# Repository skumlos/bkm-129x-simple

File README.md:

A simplified version of the BKM-129X compatible board.

Revision B

Should be able to be created at $25-30, with the ADG1611 being the most expensive component.

This requires an Arduino Nano v3 loaded with the latest BKM-129X-MCU code from https://github.com/skumlos/bkm-129x-mcu

For more information go to https://immerhax.com/?p=422

You are welcome to clone, produce and sell hardware based on this. Please keep changes and so on open source.

Cool kids give credit where due.

Thanks goes out to Nick Carney and Bob from RetroRGB for rigorious testing!

--------

Compatibility list and tested consoles (including issues):

PVM-9L2
- SNES (US region, CSYNC)
- Mega Drive 2 (EU region, 60 Hz modded with DFO for "true" 60 Hz, CSYNC)
- Master System 1 (EU region, 60 Hz modded with DFO for "true" 60 Hz, CSYNC)
- PC-Engine (White, with THS7374 external RGB amp, CSYNC)

BVM-D14
- Genesis 1 (60 Hz, CSYNC)

BVM-D9
- Nomad (60 Hz, Triple bypass modded, CSYNC)
- SNES (US region, CSYNC)
- Master System (60 Hz, sync issues like original 129X)
- TurboGrafx/PC-Engine (60 Hz, sync issues like original 129X)

---------

Board revision history:

C: Rearranged some components for nicer layout

B: Added R29, R30, R31 to compensate for overbrightness

A: Changed R9 to 0 Ohm / jumper

---------

Copyright © 2020 Martin Hejnfelt <martin@hejnfelt.com>
This work is free. You can redistribute it and/or modify it under the
terms of the Do What The Fuck You Want To Public License, Version 2,
as published by Sam Hocevar. See the LICENSE file for more details.

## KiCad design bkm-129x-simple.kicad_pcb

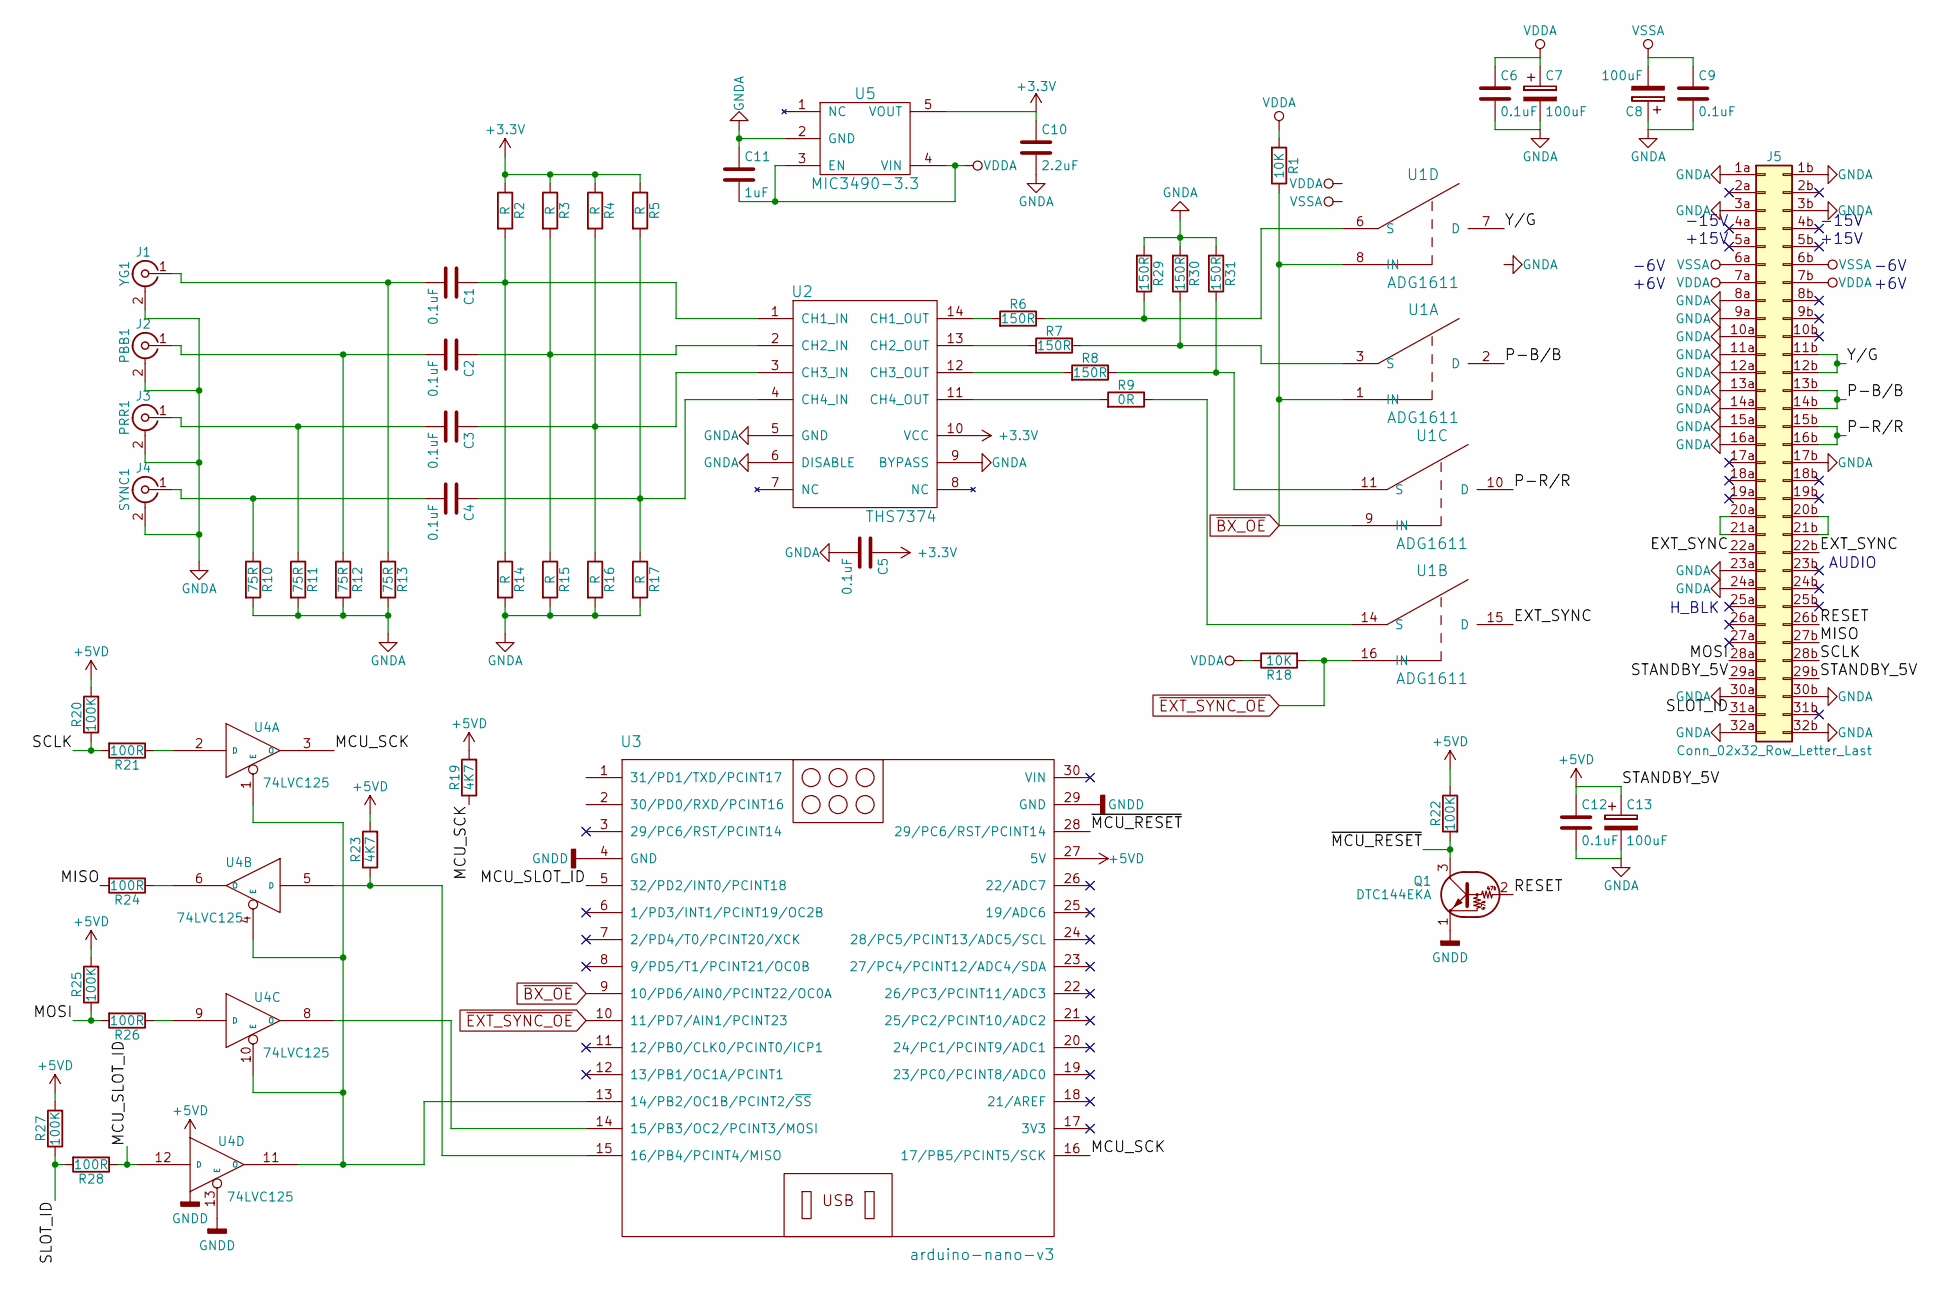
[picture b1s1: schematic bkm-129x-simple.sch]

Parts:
C1, C2, C3, C4, C5, C6, C9, C12: 0.1uF; C_0805_HandSoldering
C7, C8, C13: 100uF; CP_Elec_6.3x5.3
C10: 2.2uF; C_0805_HandSoldering
C11: 1uF; C_0805_HandSoldering
J1: YG1; BNC-THT
J2: PBB1; BNC-THT
J3: PRR1; BNC-THT
J4: SYNC1; BNC-THT
J5: Conn_02x32_Row_Letter_Last; DIN-41612-64P
Q1: DTC144EKA; SC-59_Handsoldering
R1, R18: 10K; R_0805_HandSoldering
R2, R3, R4, R5, R14, R15, R16, R17: R; R_0805_HandSoldering
R6, R7, R8, R29, R30, R31: 150R; R_0805_HandSoldering
R9: 0R; R_0805_HandSoldering
R10, R11, R12, R13: 75R; R_0805_HandSoldering
R19, R23: 4K7; R_0805_HandSoldering
R20, R22, R25, R27: 100K; R_0805_HandSoldering
R21, R24, R26, R28: 100R; R_0805_HandSoldering
U1: ADG1611; TSSOP-16_4.4x5mm_Pitch0.65mm
U2: THS7374; TSSOP-14_4.4x5mm_Pitch0.65mm
U3: arduino-nano-v3
U4: 74LVC125; TSSOP-14_4.4x5mm_Pitch0.65mm
U5: MIC3490-3.3; SOT-23-5_HandSoldering

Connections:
+5VD: C12.1, C13.1, J5.29a, J5.29b, R19.2, R20.2, R22.1, R23.2, R25.2, R27.2, U3.27 (5V), U4.14 (VCC)
/EXT_SYNC: J5.22a, J5.22b, U1.15 (D)
/MCU_SCK: R19.1, U3.16 (17/PB5/PCINT5/SCK), U4.3 (O)
/MCU_SLOT_ID: R28.1, U3.5 (32/PD2/INT0/PCINT18), U4.12 (D)
/MISO: J5.27b, R24.2
/MOSI: J5.28a, R25.1, R26.2
/P-B/B: J5.13b, J5.14b, U1.2 (D)
/P-R/R: J5.15b, J5.16b, U1.10 (D)
/RESET: J5.26b, Q1.2 (B)
/SCLK: J5.28b, R20.1, R21.2
/SLOT_ID: J5.31a, R27.1, R28.2
/Y/G: J5.11b, J5.12b, U1.7 (D)
/~MCU_RESET: Q1.3 (C), R22.2, U3.28 (29/PC6/RST/PCINT14)
unnamed: C1.1, R2.2, R14.1, U2.1 (CH1_IN)
unnamed: C1.2, J1.1 (In), R13.1
unnamed: C2.1, R3.2, R15.1, U2.2 (CH2_IN)
unnamed: C2.2, J2.1 (In), R12.1
unnamed: C3.1, R4.2, R16.1, U2.3 (CH3_IN)
unnamed: C3.2, J3.1 (In), R11.1
unnamed: C4.1, R5.2, R17.1, U2.4 (CH4_IN)
unnamed: C4.2, J4.1 (In), R10.1
unnamed: J5.20a, J5.21a
unnamed: J5.20b, J5.21b
unnamed: R6.2, U2.14 (CH1_OUT)
unnamed: R7.2, U2.13 (CH2_OUT)
unnamed: R8.2, U2.12 (CH3_OUT)
unnamed: R9.1, U1.14 (S)
unnamed: R9.2, U2.11 (CH4_OUT)
unnamed: R21.1, U4.2 (D)
unnamed: R23.1, U3.15 (16/PB4/PCINT4/MISO), U4.5 (D)
unnamed: R24.1, U4.6 (O)
unnamed: R26.1, U4.9 (D)
unnamed: R6.1, R29.1, U1.6 (S)
unnamed: R7.1, R30.1, U1.3 (S)
unnamed: R8.1, R31.1, U1.11 (S)
unnamed: U3.13 (14/PB2/OC1B/PCINT2/~SS), U4.1 (E), U4.4 (E), U4.10 (E), U4.11 (O)
unnamed: U3.14 (15/PB3/OC2/PCINT3/MOSI), U4.8 (O)
VDD: C6.1, C7.1, C11.2, J5.7a, J5.7b, R1.2, R18.1, U1.13 (VDD), U5.3 (EN), U5.4 (VIN)
VSS: C8.2, C9.1, J5.6a, J5.6b, U1.4 (VSS)
~BX_OE: R1.1, U1.1 (IN), U1.8 (IN), U1.9 (IN), U3.9 (10/PD6/AIN0/PCINT22/OC0A)
~EXT_SYNC_OE: R18.2, U1.16 (IN), U3.10 (11/PD7/AIN1/PCINT23)

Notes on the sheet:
-15V
+15V
-6V
+6V
AUDIO
H_BLK

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
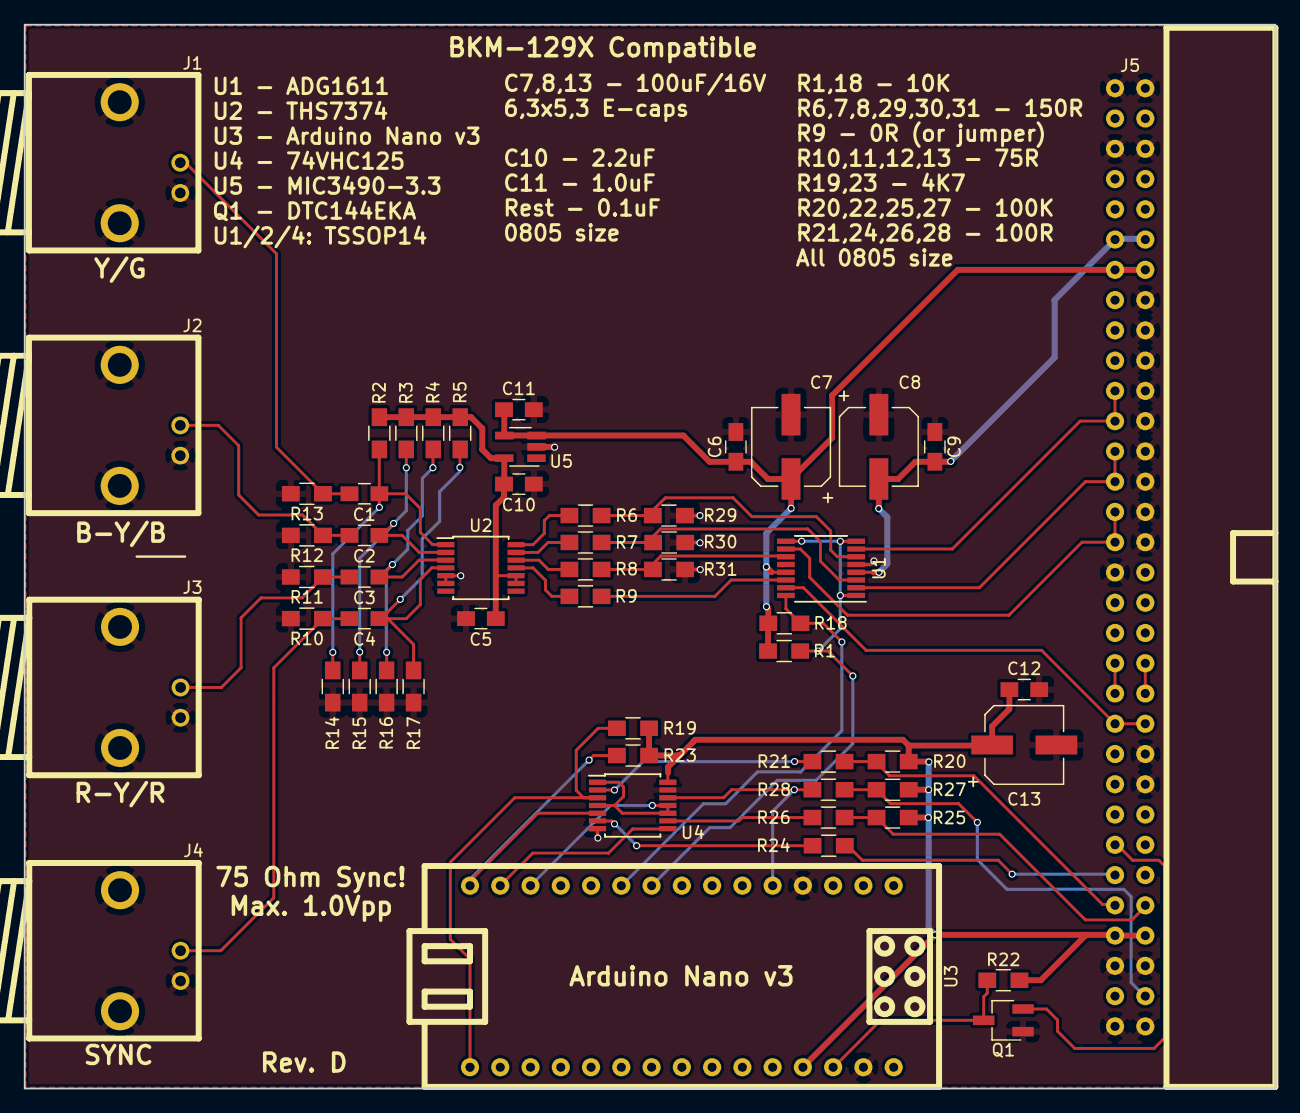
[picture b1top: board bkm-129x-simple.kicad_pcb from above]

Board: 2 copper layers, 105.0 x 89.3 mm, 55 parts (0 on the bottom side), 43 nets.

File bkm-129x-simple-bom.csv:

Id,Designator,Package,Quantity,Designation,Supplier and ref
1,"C1,C2,C3,C4,C5,C6,C9,C12",C_0805_HandSoldering,8,0.1uF,
2,"C7,C8,C13",CP_Elec_6.3x5.3,3,100uF,
3,J1,BNC-THT,1,YG1,ADAM TECH RF1-01B-D-00-75 (but others are compatible)
4,J2,BNC-THT,1,PBB1,ADAM TECH RF1-01B-D-00-75 (but others are compatible)
5,J3,BNC-THT,1,PRR1,ADAM TECH RF1-01B-D-00-75 (but others are compatible)
6,J4,BNC-THT,1,SYNC1,ADAM TECH RF1-01B-D-00-75 (but others are compatible)
7,J5,DIN-41612-64P,1,Conn_02x32_Row_Letter_Last,Amphenol T821-1-64-R1 (but any 64-pin (2x32) pin header with 2.54 mm pitch seems good)
8,Q1,SC-59_Handsoldering,1,DTC144EKA,
9,"R1,R18",R_0805_HandSoldering,2,10K,
10,"R2,R3,R4,R5,R14,R15,R16,R17",R_0805_HandSoldering,8,R,
11,"R6,R7,R8,R29,R30,R31",R_0805_HandSoldering,6,150R,
12,R9,R_0805_HandSoldering,1,0R,
13,"R10,R11,R12,R13",R_0805_HandSoldering,4,75R,
14,"R20,R22,R25,R27",R_0805_HandSoldering,4,100K,
15,"R21,R24,R26,R28",R_0805_HandSoldering,4,100R,
16,"R23,R19",R_0805_HandSoldering,2,4K7,
17,U1,TSSOP-16_4.4x5mm_Pitch0.65mm,1,ADG1611,
18,U3,arduino-nano-v3,1,arduino-nano-v3,
19,U2,TSSOP-14_4.4x5mm_Pitch0.65mm,1,THS7374,
20,U4,TSSOP-14_4.4x5mm_Pitch0.65mm,1,74VHC125,Note 74VHC125
21,C10,C_0805_HandSoldering,1,2.2uF,
22,C11,C_0805_HandSoldering,1,1uF,
23,U5,SOT-23-5_HandSoldering,1,MIC3490-3.3,

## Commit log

2020-02-17 Added readme and some info on silkscreen
2020-02-19 Updated and fixed silkscreen BOM
2020-02-19 Fixed more BOM mistakes
2020-02-19 Fixed MIC3940 -> MIC3490
2020-03-16 Added revision, compatibility and credits
2020-03-16 Added revision history for the future
2020-03-17 Updated compatibility list
2020-03-18 Fixed R9 to 0 Ohm on PCB also
2020-03-18 Added BOM
2020-04-01 Added overbrightness fix
2020-04-01 Board revision B
2020-04-01 Add LICENSE
2020-04-01 Updated BOM
2020-06-28 Rearranged some components, bumped to rev. C
2020-06-28 Added cache
2021-05-09 Rev. D: THS7374 LPF, Kicad 5
2021-05-09 Add plot
